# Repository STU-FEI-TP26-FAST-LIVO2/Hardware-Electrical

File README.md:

# TP-Hardware

Hardvérová časť projektu vytvorená v Autodesk EAGLE / Fusion Electronics.
Repozitár obsahuje schémy zapojení, návrh PCB pre Bluepill dosku a exportované
výrobné podklady.

## Obsah repozitára

```text
.
├── Bluepill_zapojenie/
│   ├── src/       # EAGLE schéma, board a CAM/job/projektové súbory
│   └── exports/   # PDF exporty schém/dosky a Gerber ZIP
├── IMU_zapojenie/
│   ├── src/       # EAGLE schéma zapojenia STM/Nucleo a IMU konektora
│   └── exports/   # PDF a PNG exporty schémy
├── Komunikacne_schemy/
│   ├── TP_BlokovaSchema.drawio
│   └── TP_BlokovaSchema.png
└── MAX3232_zapojenie/
    ├── src/       # EAGLE schéma zapojenia STM/Nucleo a MAX3232 rozhrania
    └── exports/   # PDF a PNG exporty schémy
```

Exportované náhľady a dokumenty:

- `Bluepill_zapojenie/exports/` - PDF schémy/dosky a
  `full_schematic_board_GERBER.zip`.
- `IMU_zapojenie/exports/` - `STM_IMU.png`,
  `Zapojenie_STM_EPSON_A4.pdf`, `Zapojenie_STM_EPSON_A5.pdf`.
- `MAX3232_zapojenie/exports/` - `MAX3232.png`, `MAX3232_A4.pdf`,
  `MAX3232_A5.pdf`.
- `Komunikacne_schemy/` - `TP_BlokovaSchema.drawio` a
  `TP_BlokovaSchema.png`.

## Moduly

### Bluepill_zapojenie

Hlavná doska okolo modulu Blue Pill. V repozitári sú dve varianty schémy:

- `src/BLUEPILL_full_schematic.sch` - schéma s Blue Pill modulom, IMU konektorom,
  konektorom `J3` a vlastným symbolom `MAX3232_CUSTOM`.
- `src/BLUEPILL_full_schematic for BRD.sch` - schéma naviazaná na PCB layout.
- `src/BLUEPILL_full_schematic for BRD.brd` - EAGLE board súbor.
- `exports/full_schematic_board_GERBER.zip` - export pre výrobu dosky.

Gerber archív obsahuje vrstvy medi, masky, potlače, pasty, profil dosky,
drill súbor a základné assembly výstupy.

### IMU_zapojenie

Schéma pre prepojenie dosky `NUCLEO-F303K8` s IMU konektorom. Hlavný súbor:

- `src/Zapojenie_STM_EPSON.sch`

Pre správne zapojenie IMU (Inertial Measurement Unit) bola použitá oficiálna dokumentácia k doskám typu **24 CLICK**. Z tejto dokumentácie boli presne obkreslené polohy a správne rozstupové rozmedzia pinov (cez poskytnutý STL a footprint), aby bola zaručená mechanická a elektrická kompatibilita.
Referenčný modul: [6DOF IMU 24 Click](https://www.mikroe.com/6dof-imu-24-click?srsltid=AfmBOopXifQUx5eslR1XnWNQ_cjDjcsM_FVL3atVTf2INUSxUIHtFeJk)

### MAX3232_zapojenie

Schéma pre prepojenie dosky `NUCLEO-F303K8` a konektorovej časti MAX3232/RS-232. 
Hlavný súbor:

- `src/MAX3232_zapojenie.sch`

### Komunikacne_schemy

Blokové/komunikačné schémy systému. Priečinok obsahuje editovateľný Draw.io
súbor a exportovaný PNG náhľad:

- `TP_BlokovaSchema.drawio`
- `TP_BlokovaSchema.png`

## Výpočet napájania a dimenzovanie akumulátora

Na zabezpečenie spoľahlivej prevádzky prenosného systému po dobu minimálne 30 minút bol stanovený celkový energetický odber a vypočítaná požadovaná kapacita napájacieho zdroja.

- **Celkový príkon systému ($P_{total}$):** Súčet maximálnych príkonov jednotlivých komponentov integrovaných v systéme.
  $P_{total} = 60 + 9 + 3.4 + 0.05 = 72.5 \text{ W}$
- **Požadovaná energia ($E$):** Pre požadovanú dobu prevádzky $t = 0.5 \text{ h}$ bol do výpočtu zahrnutý bezpečnostný koeficient $1.25$ (25 % rezerva na straty meničov a degradáciu článkov) a výpočtový príkon bol zaokrúhlený na $75 \text{ W}$.
  $E = 75 \text{ W} \cdot 0.5 \text{ h} \cdot 1.25 \approx 50 \text{ Wh}$
- **Požadovaná kapacita ($C$):** Pri dimenzovaní na uvažované systémové napätie 12 V.
  $C = \frac{50 \text{ Wh}}{12 \text{ V}} \approx 4.2 \text{ Ah}$

Na základe týchto parametrov a pre zaistenie dostatočnej prúdovej aj kapacitnej rezervy bol ako napájací zdroj zvolený **Li-Po (lítium-polymérový) akumulátor** v konfigurácii **4S** (nominálne napätie 14.8 V) s kapacitou **5.5 Ah** od výrobcu **Amewi**.

## Použité externé knižnice

V projekte sú použité nasledovné externé EAGLE knižnice:
- [NUCLEO-F303K8.lbr](https://github.com/martonmiklos/EAGLE-libraries/blob/master/NUCLEO-F303K8.lbr)
- [BluePill.lbr](https://github.com/sagarHackeD/STM32Bluepill_eagle/blob/master/BluePill.lbr)

## BOM na osadenie PCB

| Čo to je | Počet |
| --- | ---: |
| Káble XH2.54 samica/samec, 2-pin | 1 |
| Káble XH2.54 samica/samec, 3-pin | 2 |
| Káble XH2.54 samica/samec, 4-pin | 1 |
| Konektor XH2.54 rovný, 2-pin | 1 |
| Konektor XH2.54 rovný, 3-pin | 2 |
| Konektor XH2.54 rovný, 4-pin | 1 |
| Predlžovací USB 3.0 kábel male-female, 0.5 m | 2 |
| Kábel LiDAR DC005 samec, 2 m | 1 |
| Female piny 2.54 mm, 40 ks, 1 riadok | 2 |
| Female piny 2.54 mm, krátke, 8-pin | 2 |

- na uchytenie PCB sú pripravené 3.2 mm diery 

## Ako projekt otvoriť

1. Nainštaluj Autodesk EAGLE alebo Fusion 360 Electronics.
2. Otvor príslušný `.sch` súbor pre schému.
3. Pri Bluepill doske otvor aj `.brd` súbor s rovnakým názvom, aby schéma a PCB
   zostali synchronizované (!PRI ÚPRAVE MUSIA BYŤ OTVORENÉ OBA SÚBORY).
4. Pred ďalším exportom skontroluj ERC/DRC a CAM nastavenia v EAGLE.

## Výrobné podklady

Aktuálne exportované podklady sú v:

```text
Bluepill_zapojenie/exports/full_schematic_board_GERBER.zip
```

Pred odoslaním do výroby odporúčané kontroly:

- otvoriť Gerber súbory v nezávislom Gerber vieweri,
- skontrolovať orientáciu, obrys dosky a vŕtanie,
- overiť konektory, napájanie a mechanické rozmery,
- porovnať aktuálny `.brd` súbor s exportovaným ZIP archívom.

## Poznámky k súborom

- `.sch` - EAGLE schéma.
- `.brd` - EAGLE PCB layout.
- `.pro` - projektový súbor EAGLE.
- `.job` - CAM/export konfigurácia.
- `s#`, `b#` a podobné súbory sú automatické zálohy vytvorené programom EAGLE.

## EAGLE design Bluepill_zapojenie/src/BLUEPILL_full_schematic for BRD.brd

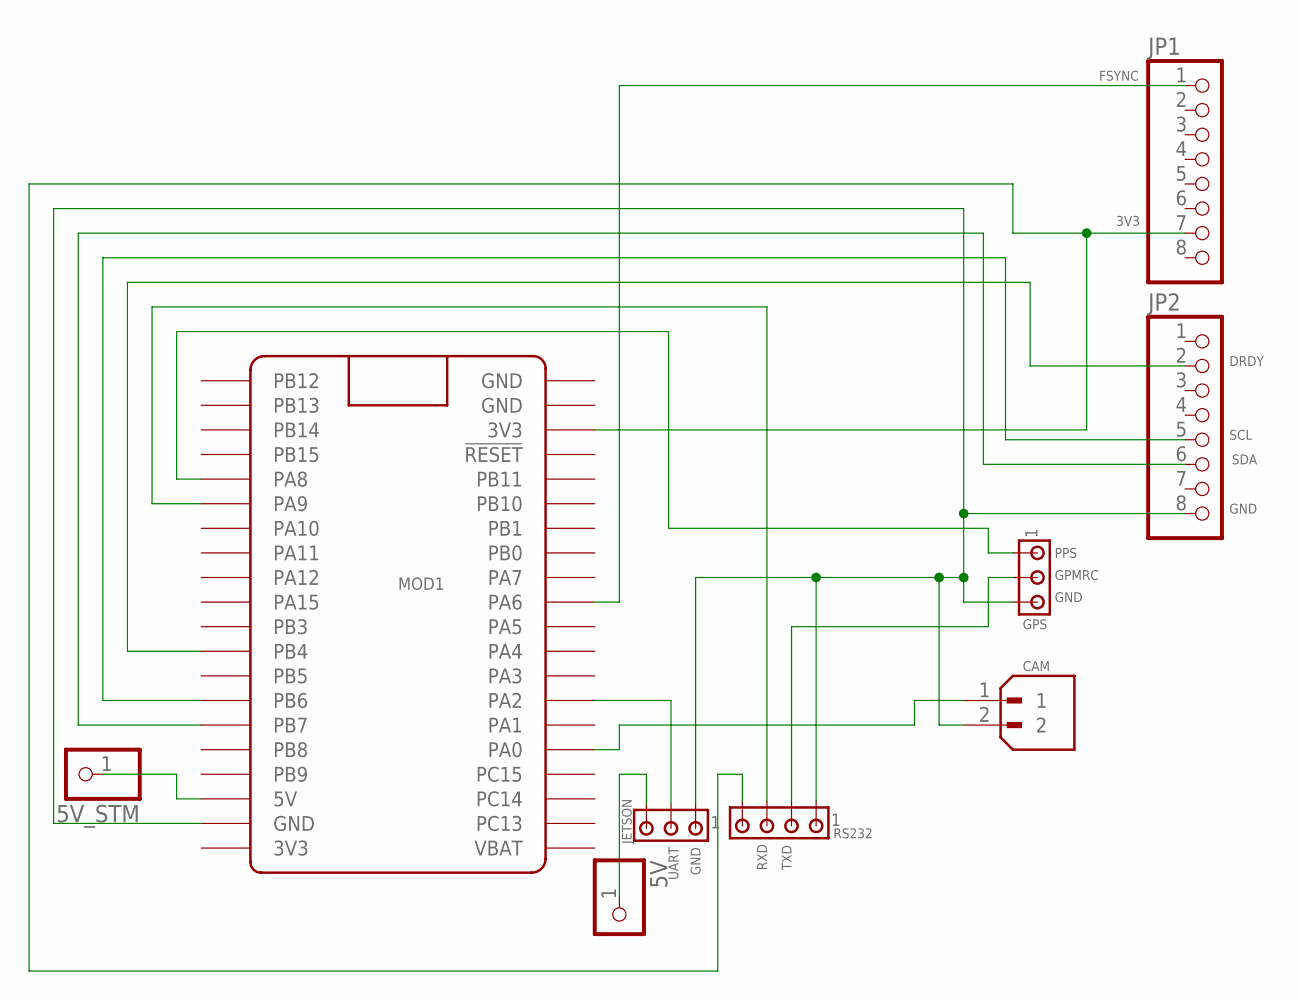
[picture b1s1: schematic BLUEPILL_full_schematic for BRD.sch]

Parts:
5V, 5V_STM: PINHD-1X1; 1X01
CAM: B2B-XH-A; JST_B2B-XH-A
GPS: MTA03-100; 10X03MTA
JETSON: MTA03-100; 10X03MTA
JP1, JP2: PINHD-1X8; 1X08
MOD1: BLUE_PILL
RS232: MTA04-100; 10X04MTA

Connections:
3V3: JP1.7, MOD1.P$23 (3V3), RS232.4
DRDY: JP2.2, MOD1.P$12 (PB4)
FSYNC: JP1.1, MOD1.P$30 (PA6)
GND: CAM.2, GPS.3, JETSON.1, JP2.8, MOD1.P$19 (GND), RS232.1
unnamed: 5V_STM.1, MOD1.P$18 (5V)
unnamed: 5V.1, JETSON.3
unnamed: CAM.1, MOD1.P$36 (PA0)
PPS: GPS.1, MOD1.P$5 (PA8)
RXD: MOD1.P$6 (PA9), RS232.3
SCL: JP2.5, MOD1.P$14 (PB6)
SDA: JP2.6, MOD1.P$15 (PB7)
TXD: GPS.2, RS232.2
UART: JETSON.2, MOD1.P$34 (PA2)

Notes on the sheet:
GND
GPMRC
UART

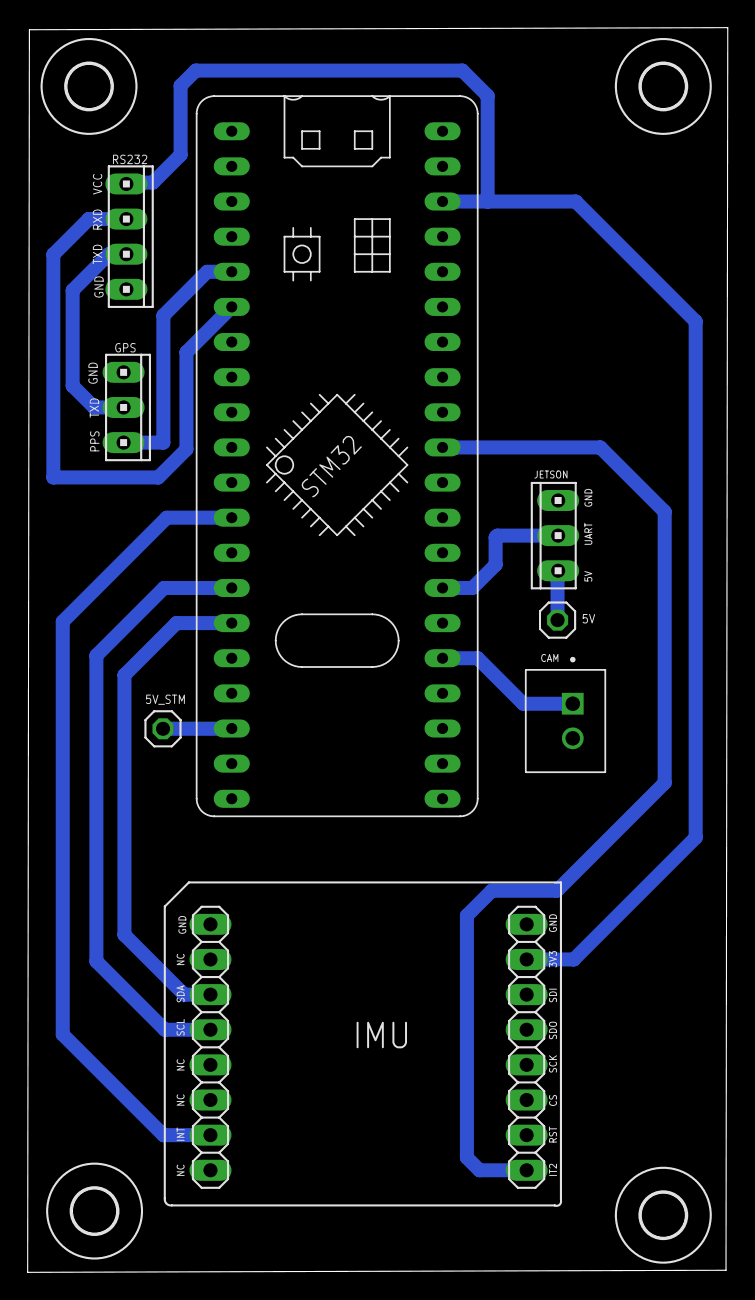
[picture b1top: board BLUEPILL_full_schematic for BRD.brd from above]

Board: 2 copper layers, 50.6 x 90.0 mm, 13 parts (0 on the bottom side), 13 nets.

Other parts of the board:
U$1, U$2, U$3, U$4: 3,2

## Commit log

2026-03-17 Schema zapojenia PPS a GPMRC LiDARu
    Vytvorená schéma zapojenia pre PPS a GPMRC LiDARu. MAX3232 riešené cez pin konektor.
2026-03-25 Upratanie
    Roztriedenie do priecinkov + pridane png exporty schem.
    Pridana aj prva schema, ktora bola pridana na yzlu branch predtym.
2026-03-27 Pridané PDF exporty
    Pridané PDF exporty v A4 aj A5 formáte.
2026-04-09 PCB + full schematic
    Navrh DPS, zapojenie full schemy Bluepill, IMU, GPS, RS232.
    Navrh vlastnej znacky pre RS232.
2026-04-10 Vizualizacia board
2026-04-30 BRD schema final version
    added IMU to PCB + CAM and UART connectors. 5V VCC from USB to Bluepill
2026-05-26 Final push
    schemy, exporty final verzie
2026-05-26 README
    pridane readme
2026-05-27 Pridana komunikacna schema
    pridana komunikacna schema plus mensia uprava hlavnej schemy
2026-05-28 README update
    Pridane odkazy do readme na pouzite externe kniznice + vypocet potrebnej kapacity baterie
2026-05-29 Diakritika
    Pridana diakritika do readme
2026-05-29 Fix formatting of project title in README
